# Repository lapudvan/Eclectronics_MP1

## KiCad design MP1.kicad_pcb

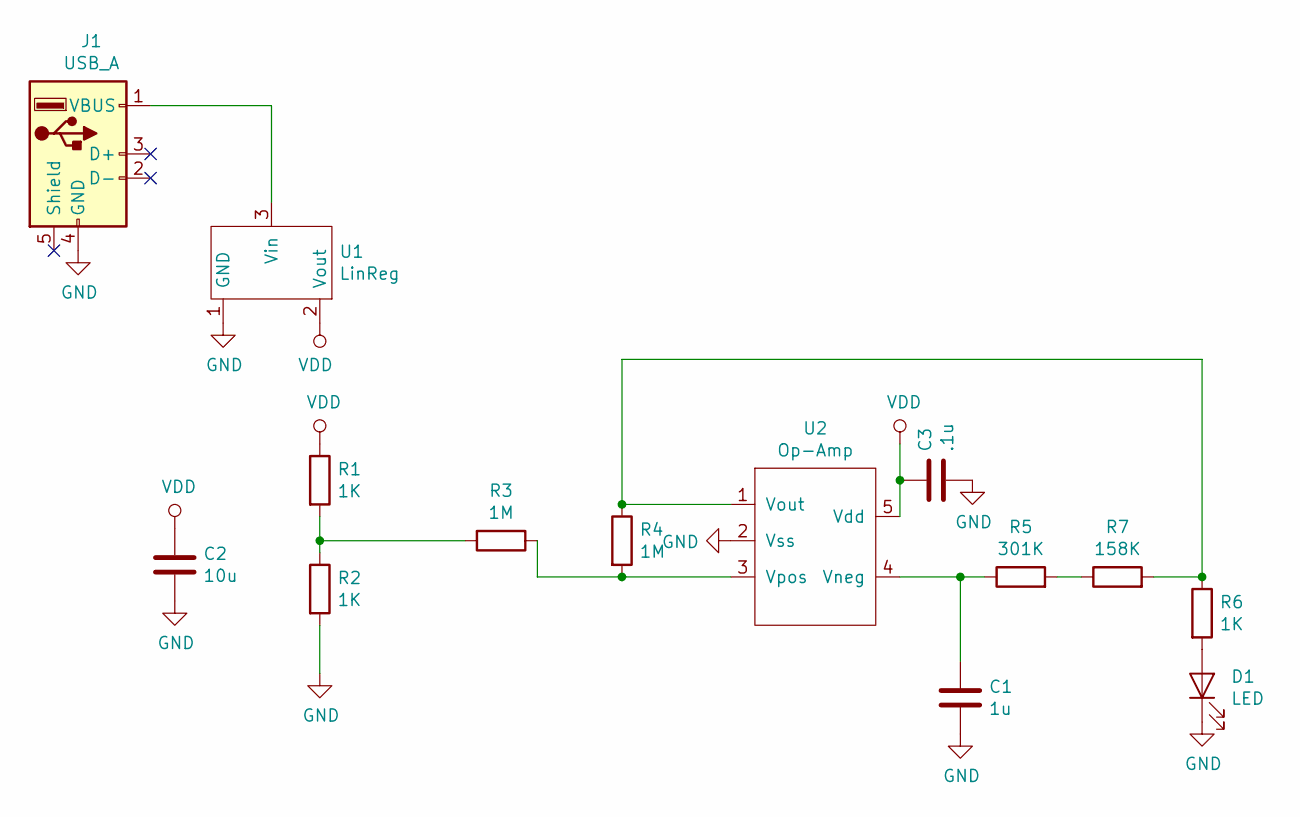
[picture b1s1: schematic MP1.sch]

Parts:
C1: 1u; C_0603_1608Metric
C2: 10u; C_0805_2012Metric
C3: .1u; C_0603_1608Metric
D1: LED
J1: USB_A; USB
R1, R2, R6: 1K; C_0603_1608Metric
R3, R4: 1M; C_0603_1608Metric
R5: 301K; C_0603_1608Metric
R7: 158K; C_0603_1608Metric
U1: LinReg; RegLin
U2: Op-Amp; SOT23

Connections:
GND: C1.2, C2.2, C3.2, D1.1 (K), J1.4 (GND), R2.2, U1.1 (GND), U2.2 (Vss)
unnamed: C1.1, R5.1, U2.4 (Vneg)
unnamed: D1.2 (A), R6.2
unnamed: J1.1 (VBUS), U1.3 (Vin)
unnamed: R1.2, R2.1, R3.2
unnamed: R3.1, R4.2, U2.3 (Vpos)
unnamed: R4.1, R6.1, R7.2, U2.1 (Vout)
unnamed: R5.2, R7.1
VDD: C2.1, C3.1, R1.1, U1.2 (Vout), U2.5 (Vdd)

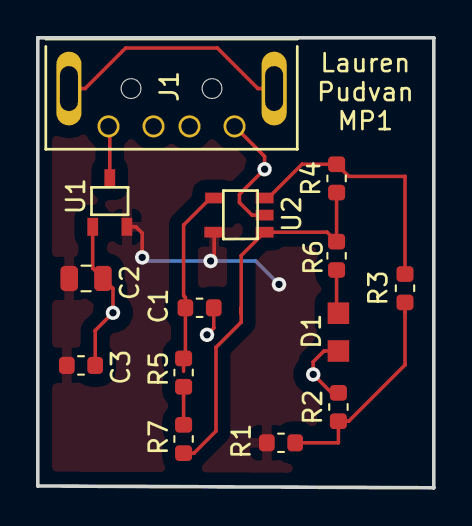
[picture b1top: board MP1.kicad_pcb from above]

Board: 2 copper layers, 22.0 x 25.0 mm, 14 parts (0 on the bottom side), 9 nets.

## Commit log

2019-02-11 Uploading everything for MP1
